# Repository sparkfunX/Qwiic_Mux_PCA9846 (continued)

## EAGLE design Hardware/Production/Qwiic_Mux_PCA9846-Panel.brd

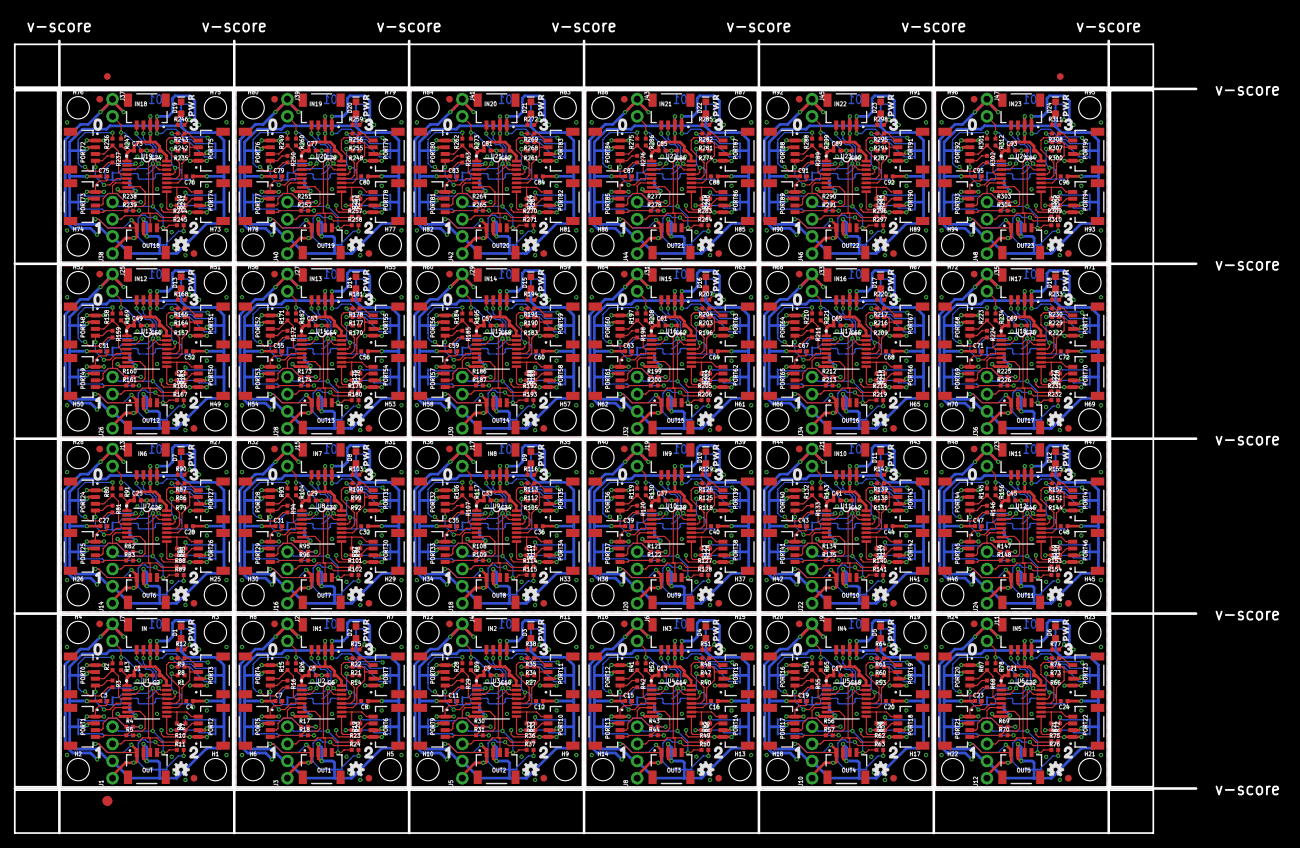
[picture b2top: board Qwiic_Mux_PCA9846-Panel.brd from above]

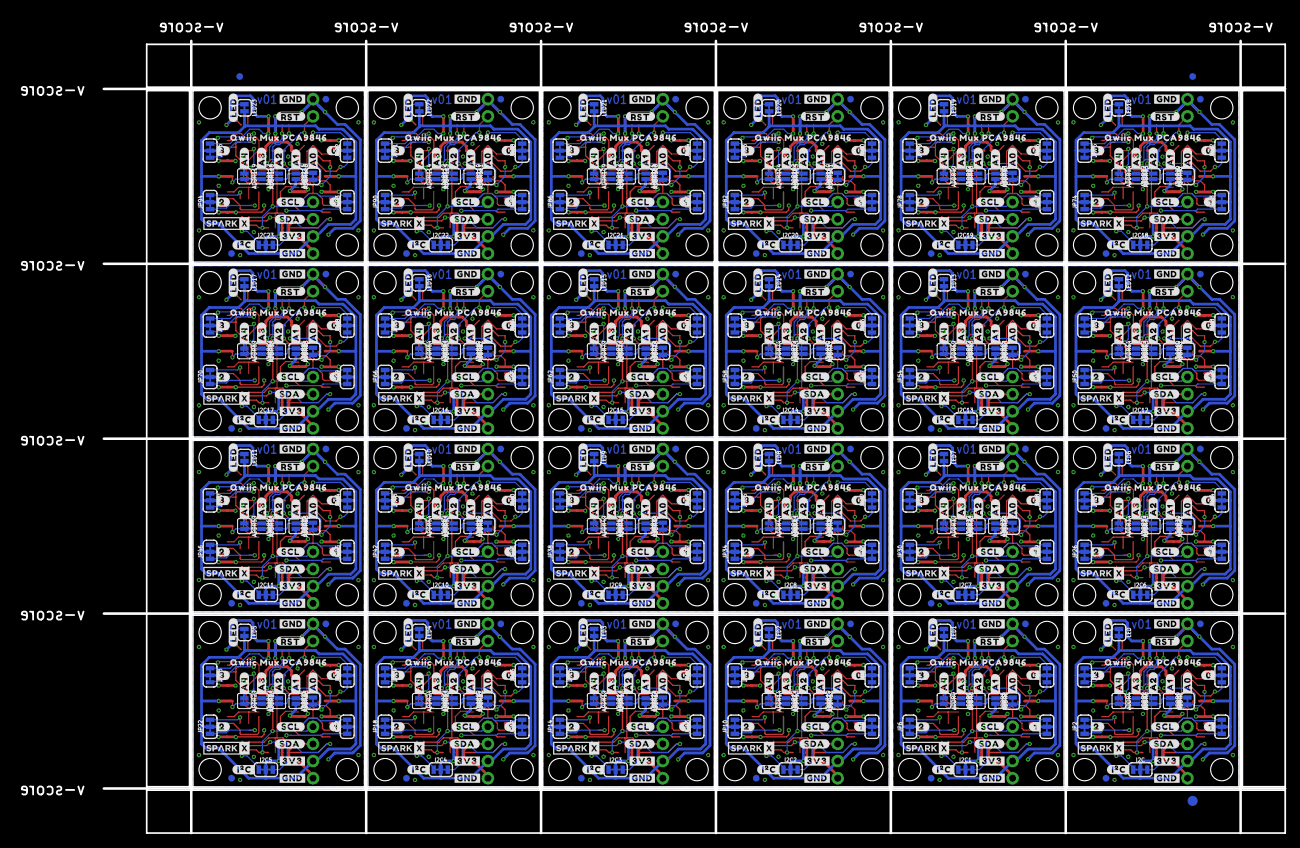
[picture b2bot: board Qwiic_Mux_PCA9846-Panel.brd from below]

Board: 2 copper layers, 175.0 x 117.3 mm, 1710 parts (771 on the bottom side), 648 nets.

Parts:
ADDR0, ADDR5, ADDR10, ADDR15, ADDR20, ADDR25, ADDR30, ADDR35, ADDR40, ADDR45, ADDR50, ADDR55, ADDR60, ADDR65, ADDR70, ADDR75, ADDR80, ADDR85, ADDR90, ADDR95, ADDR100, ADDR105, ADDR110, ADDR115: JUMPER-SMT_2_NC_TRACE_SILK; SMT-JUMPER_2_NC_TRACE_SILK
ADDR1, ADDR2, ADDR3, ADDR4, ADDR6, ADDR7, ADDR8, ADDR9, ADDR11, ADDR12, ADDR13, ADDR14, ADDR16, ADDR17, ADDR18, ADDR19, ADDR21, ADDR22, ADDR23, ADDR24, ADDR26, ADDR27, ADDR28, ADDR29, ADDR31, ADDR32, ADDR33, ADDR34, ADDR36, ADDR37, ADDR38, ADDR39, ADDR41, ADDR42, ADDR43, ADDR44, ADDR46, ADDR47, ADDR48, ADDR49, ADDR51, ADDR52, ADDR53, ADDR54, ADDR56, ADDR57, ADDR58, ADDR59, ADDR61, ADDR62, ADDR63, ADDR64, ADDR66, ADDR67, ADDR68, ADDR69, ADDR71, ADDR72, ADDR73, ADDR74, ADDR76, ADDR77, ADDR78, ADDR79, ADDR81, ADDR82, ADDR83, ADDR84, ADDR86, ADDR87, ADDR88, ADDR89, ADDR91, ADDR92, ADDR93, ADDR94, ADDR96, ADDR97, ADDR98, ADDR99, ADDR101, ADDR102, ADDR103, ADDR104, ADDR106, ADDR107, ADDR108, ADDR109, ADDR111, ADDR112, ADDR113, ADDR114, ADDR116, ADDR117, ADDR118, ADDR119: JUMPER-SMT_2_NO_SILK; SMT-JUMPER_2_NO_SILK
C1, C3, C4, C5, C7, C8, C9, C11, C12, C13, C15, C16, C17, C19, C20, C21, C23, C24, C25, C27, C28, C29, C31, C32, C33, C35, C36, C37, C39, C40, C41, C43, C44, C45, C47, C48, C49, C51, C52, C53, C55, C56, C57, C59, C60, C61, C63, C64, C65, C67, C68, C69, C71, C72, C73, C75, C76, C77, C79, C80, C81, C83, C84, C85, C87, C88, C89, C91, C92, C93, C95, C96: 2.2uF; 0402-TIGHT
C2, C6, C10, C14, C18, C22, C26, C30, C34, C38, C42, C46, C50, C54, C58, C62, C66, C70, C74, C78, C82, C86, C90, C94: 0.1uF; 0402-TIGHT
D1, D2, D3, D4, D5, D6, D7, D8, D9, D10, D11, D12, D13, D14, D15, D16, D17, D18, D19, D20, D21, D22, D23, D24: RED; LED-0603
E$1, E$2, E$3, E$4: FIDUCIAL-1X2
E$5, E$6: FIDUCIAL-1.5X3
FD1, FD2, FD3, FD4, FD5, FD6, FD7, FD8, FD9, FD10, FD11, FD12, FD13, FD14, FD15, FD16, FD17, FD18, FD19, FD20, FD21, FD22, FD23, FD24, FD25, FD26, FD27, FD28, FD29, FD30, FD31, FD32, FD33, FD34, FD35, FD36, FD37, FD38, FD39, FD40, FD41, FD42, FD43, FD44, FD45, FD46, FD47, FD48, FD49, FD50, FD51, FD52, FD53, FD54, FD55, FD56, FD57, FD58, FD59, FD60, FD61, FD62, FD63, FD64, FD65, FD66, FD67, FD68, FD69, FD70, FD71, FD72, FD73, FD74, FD75, FD76, FD77, FD78, FD79, FD80, FD81, FD82, FD83, FD84, FD85, FD86, FD87, FD88, FD89, FD90, FD91, FD92, FD93, FD94, FD95, FD96: FIDUCIAL1X2; FIDUCIAL-1X2
H1, H2, H3, H4, H5, H6, H7, H8, H9, H10, H11, H12, H13, H14, H15, H16, H17, H18, H19, H20, H21, H22, H23, H24, H25, H26, H27, H28, H29, H30, H31, H32, H33, H34, H35, H36, H37, H38, H39, H40, H41, H42, H43, H44, H45, H46, H47, H48, H49, H50, H51, H52, H53, H54, H55, H56, H57, H58, H59, H60, H61, H62, H63, H64, H65, H66, H67, H68, H69, H70, H71, H72, H73, H74, H75, H76, H77, H78, H79, H80, H81, H82, H83, H84, H85, H86, H87, H88, H89, H90, H91, H92, H93, H94, H95, H96: STAND-OFF
I2C, I2C1, I2C2, I2C3, I2C4, I2C5, I2C6, I2C7, I2C8, I2C9, I2C10, I2C11, I2C12, I2C13, I2C14, I2C15, I2C16, I2C17, I2C18, I2C19, I2C20, I2C21, I2C22, I2C23: JUMPER-SMT_3_2-NC_TRACE_SILK; SMT-JUMPER_3_2-NC_TRACE_SILK
IN, IN1, IN2, IN3, IN4, IN5, IN6, IN7, IN8, IN9, IN10, IN11, IN12, IN13, IN14, IN15, IN16, IN17, IN18, IN19, IN20, IN21, IN22, IN23: QWIIC_RIGHT_ANGLE; JST04_1MM_RA
J1, J3, J5, J8, J10, J12, J14, J16, J18, J20, J22, J24, J26, J28, J30, J32, J34, J36, J38, J40, J42, J44, J46, J48: 1X04_NO_SILK
J2, J4, J6, J7, J9, J11, J13, J15, J17, J19, J21, J23, J25, J27, J29, J31, J33, J35, J37, J39, J41, J43, J45, J47: 1X02_NO_SILK
JP0, JP1, JP2, JP3, JP4, JP5, JP6, JP7, JP8, JP9, JP10, JP11, JP12, JP13, JP14, JP15, JP16, JP17, JP18, JP19, JP20, JP21, JP22, JP23, JP24, JP25, JP26, JP27, JP28, JP29, JP30, JP31, JP32, JP33, JP34, JP35, JP36, JP37, JP38, JP39, JP40, JP41, JP42, JP43, JP44, JP45, JP46, JP47, JP48, JP49, JP50, JP51, JP52, JP53, JP54, JP55, JP56, JP57, JP58, JP59, JP60, JP61, JP62, JP63, JP64, JP65, JP66, JP67, JP68, JP69, JP70, JP71, JP72, JP73, JP74, JP75, JP76, JP77, JP78, JP79, JP80, JP81, JP82, JP83, JP84, JP85, JP86, JP87, JP88, JP89, JP90, JP91, JP92, JP93, JP94, JP95: JUMPER-SMT_3_2-NC_TRACE_SILK; SMT-JUMPER_3_2-NC_TRACE_SILK
LED, LED1, LED2, LED3, LED4, LED5, LED6, LED7, LED8, LED9, LED10, LED11, LED12, LED13, LED14, LED15, LED16, LED17, LED18, LED19, LED20, LED21, LED22, LED23: JUMPER-SMT_2_NC_TRACE_SILK; SMT-JUMPER_2_NC_TRACE_SILK
LOGO1, LOGO2, LOGO3, LOGO4, LOGO5, LOGO6, LOGO7, LOGO8, LOGO9, LOGO10, LOGO11, LOGO12, LOGO13, LOGO14, LOGO15, LOGO16, LOGO17, LOGO18, LOGO19, LOGO20, LOGO21, LOGO22, LOGO23, LOGO24: OSHW-LOGOMINI; OSHW-LOGO-MINI
OUT, OUT1, OUT2, OUT3, OUT4, OUT5, OUT6, OUT7, OUT8, OUT9, OUT10, OUT11, OUT12, OUT13, OUT14, OUT15, OUT16, OUT17, OUT18, OUT19, OUT20, OUT21, OUT22, OUT23: QWIIC_RIGHT_ANGLE; JST04_1MM_RA
PORT0, PORT1, PORT2, PORT3, PORT4, PORT5, PORT6, PORT7, PORT8, PORT9, PORT10, PORT11, PORT12, PORT13, PORT14, PORT15, PORT16, PORT17, PORT18, PORT19, PORT20, PORT21, PORT22, PORT23, PORT24, PORT25, PORT26, PORT27, PORT28, PORT29, PORT30, PORT31, PORT32, PORT33, PORT34, PORT35, PORT36, PORT37, PORT38, PORT39, PORT40, PORT41, PORT42, PORT43, PORT44, PORT45, PORT46, PORT47, PORT48, PORT49, PORT50, PORT51, PORT52, PORT53, PORT54, PORT55, PORT56, PORT57, PORT58, PORT59, PORT60, PORT61, PORT62, PORT63, PORT64, PORT65, PORT66, PORT67, PORT68, PORT69, PORT70, PORT71, PORT72, PORT73, PORT74, PORT75, PORT76, PORT77, PORT78, PORT79, PORT80, PORT81, PORT82, PORT83, PORT84, PORT85, PORT86, PORT87, PORT88, PORT89, PORT90, PORT91, PORT92, PORT93, PORT94, PORT95: QWIIC_RIGHT_ANGLE; JST04_1MM_RA
R1, R13, R14, R26, R27, R39, R40, R52, R53, R65, R66, R78, R79, R91, R92, R104, R105, R117, R118, R130, R131, R143, R144, R156, R157, R169, R170, R182, R183, R195, R196, R208, R209, R221, R222, R234, R235, R247, R248, R260, R261, R273, R274, R286, R287, R299, R300, R312: 100k; 0402-TIGHT
R2, R3, R4, R5, R6, R7, R8, R9, R10, R11, R15, R16, R17, R18, R19, R20, R21, R22, R23, R24, R28, R29, R30, R31, R32, R33, R34, R35, R36, R37, R41, R42, R43, R44, R45, R46, R47, R48, R49, R50, R54, R55, R56, R57, R58, R59, R60, R61, R62, R63, R67, R68, R69, R70, R71, R72, R73, R74, R75, R76, R80, R81, R82, R83, R84, R85, R86, R87, R88, R89, R93, R94, R95, R96, R97, R98, R99, R100, R101, R102, R106, R107, R108, R109, R110, R111, R112, R113, R114, R115, R119, R120, R121, R122, R123, R124, R125, R126, R127, R128, R132, R133, R134, R135, R136, R137, R138, R139, R140, R141, R145, R146, R147, R148, R149, R150, R151, R152, R153, R154, R158, R159, R160, R161, R162, R163, R164, R165, R166, R167, R171, R172, R173, R174, R175, R176, R177, R178, R179, R180, R184, R185, R186, R187, R188, R189, R190, R191, R192, R193, R197, R198, R199, R200, R201, R202, R203, R204, R205, R206, R210, R211, R212, R213, R214, R215, R216, R217, R218, R219, R223, R224, R225, R226, R227, R228, R229, R230, R231, R232, R236, R237, R238, R239, R240, R241, R242, R243, R244, R245, R249, R250, R251, R252, R253, R254, R255, R256, R257, R258, R262, R263, R264, R265, R266, R267, R268, R269, R270, R271, R275, R276, R277, R278, R279, R280, R281, R282, R283, R284, R288, R289, R290, R291, R292, R293, R294, R295, R296, R297, R301, R302, R303, R304, R305, R306, R307, R308, R309, R310: 2.2k; 0402-TIGHT
R12, R25, R38, R51, R64, R77, R90, R103, R116, R129, R142, R155, R168, R181, R194, R207, R220, R233, R246, R259, R272, R285, R298, R311: 1k; 0402-TIGHT
U1, U2, U3, U4, U5, U6, U7, U8, U9, U10, U11, U12, U13, U14, U15, U16, U17, U18, U19, U20, U21, U22, U23, U24: PCA9846; SOT403-1
U$1, U$20, U$49, U$73, U$97, U$121, U$145, U$169, U$193, U$217, U$241, U$265, U$289, U$313, U$337, U$361, U$385, U$409, U$433, U$457, U$481, U$505, U$529, U$553: SPARKX-LOGO3; SPARKX-SMALL
U$2, U$26, U$50, U$74, U$98, U$122, U$146, U$170, U$194, U$218, U$242, U$266, U$290, U$314, U$338, U$362, U$386, U$410, U$434, U$458, U$482, U$506, U$530, U$554: PWR43214
U$3, U$27, U$51, U$75, U$99, U$123, U$147, U$171, U$195, U$219, U$243, U$267, U$291, U$315, U$339, U$363, U$387, U$411, U$435, U$459, U$483, U$507, U$531, U$555: 043215
U$4, U$28, U$52, U$76, U$100, U$124, U$148, U$172, U$196, U$220, U$244, U$268, U$292, U$316, U$340, U$364, U$388, U$412, U$436, U$460, U$484, U$508, U$532, U$556: 10
U$5, U$29, U$53, U$77, U$101, U$125, U$149, U$173, U$197, U$221, U$245, U$269, U$293, U$317, U$341, U$365, U$389, U$413, U$437, U$461, U$485, U$509, U$533, U$557: 211
U$6, U$30, U$54, U$78, U$102, U$126, U$150, U$174, U$198, U$222, U$246, U$270, U$294, U$318, U$342, U$366, U$390, U$414, U$438, U$462, U$486, U$510, U$534, U$558: 3212
U$7, U$31, U$55, U$79, U$103, U$127, U$151, U$175, U$199, U$223, U$247, U$271, U$295, U$319, U$343, U$367, U$391, U$415, U$439, U$463, U$487, U$511, U$535, U$559: ##RST##8
U$8, U$32, U$56, U$80, U$104, U$128, U$152, U$176, U$200, U$224, U$248, U$272, U$296, U$320, U$344, U$368, U$392, U$416, U$440, U$464, U$488, U$512, U$536, U$560: #0#9
U$9, U$33, U$57, U$81, U$105, U$129, U$153, U$177, U$201, U$225, U$249, U$273, U$297, U$321, U$345, U$369, U$393, U$417, U$441, U$465, U$489, U$513, U$537, U$561: #1#9
U$10, U$34, U$58, U$82, U$106, U$130, U$154, U$178, U$202, U$226, U$250, U$274, U$298, U$322, U$346, U$370, U$394, U$418, U$442, U$466, U$490, U$514, U$538, U$562: #2#9
U$11, U$35, U$59, U$83, U$107, U$131, U$155, U$179, U$203, U$227, U$251, U$275, U$299, U$323, U$347, U$371, U$395, U$419, U$443, U$467, U$491, U$515, U$539, U$563: #3#9
U$12, U$36, U$60, U$84, U$108, U$132, U$156, U$180, U$204, U$228, U$252, U$276, U$300, U$324, U$348, U$372, U$396, U$420, U$444, U$468, U$492, U$516, U$540, U$564: #3V3#7
U$13, U$37, U$61, U$85, U$109, U$133, U$157, U$181, U$205, U$229, U$253, U$277, U$301, U$325, U$349, U$373, U$397, U$421, U$445, U$469, U$493, U$517, U$541, U$565: #A0#0
U$14, U$38, U$62, U$86, U$110, U$134, U$158, U$182, U$206, U$230, U$254, U$278, U$302, U$326, U$350, U$374, U$398, U$422, U$446, U$470, U$494, U$518, U$542, U$566: #A1#1
U$15, U$39, U$63, U$87, U$111, U$135, U$159, U$183, U$207, U$231, U$255, U$279, U$303, U$327, U$351, U$375, U$399, U$423, U$447, U$471, U$495, U$519, U$543, U$567: #A2#2
U$16, U$40, U$64, U$88, U$112, U$136, U$160, U$184, U$208, U$232, U$256, U$280, U$304, U$328, U$352, U$376, U$400, U$424, U$448, U$472, U$496, U$520, U$544, U$568: #A3#3
U$17, U$41, U$65, U$89, U$113, U$137, U$161, U$185, U$209, U$233, U$257, U$281, U$305, U$329, U$353, U$377, U$401, U$425, U$449, U$473, U$497, U$521, U$545, U$569: #A4#4
U$18, U$19, U$42, U$43, U$66, U$67, U$90, U$91, U$114, U$115, U$138, U$139, U$162, U$163, U$186, U$187, U$210, U$211, U$234, U$235, U$258, U$259, U$282, U$283, U$306, U$307, U$330, U$331, U$354, U$355, U$378, U$379, U$402, U$403, U$426, U$427, U$450, U$451, U$474, U$475, U$498, U$499, U$522, U$523, U$546, U$547, U$570, U$571: #GND#7
U$21, U$44, U$68, U$92, U$116, U$140, U$164, U$188, U$212, U$236, U$260, U$284, U$308, U$332, U$356, U$380, U$404, U$428, U$452, U$476, U$500, U$524, U$548, U$572: #SCL#5
U$22, U$45, U$69, U$93, U$117, U$141, U$165, U$189, U$213, U$237, U$261, U$285, U$309, U$333, U$357, U$381, U$405, U$429, U$453, U$477, U$501, U$525, U$549, U$573: #SDA#6
U$23, U$46, U$70, U$94, U$118, U$142, U$166, U$190, U$214, U$238, U$262, U$286, U$310, U$334, U$358, U$382, U$406, U$430, U$454, U$478, U$502, U$526, U$550, U$574: #LED#0
U$24, U$47, U$71, U$95, U$119, U$143, U$167, U$191, U$215, U$239, U$263, U$287, U$311, U$335, U$359, U$383, U$407, U$431, U$455, U$479, U$503, U$527, U$551, U$575: QWIIC_MUX_PCA98461
U$25, U$48, U$72, U$96, U$120, U$144, U$168, U$192, U$216, U$240, U$264, U$288, U$312, U$336, U$360, U$384, U$408, U$432, U$456, U$480, U$504, U$528, U$552, U$576: #I�C#0

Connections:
3.3V: ADDR3.2, ADDR4.2, C1.1, C2.1, C3.1, C4.1, I2C.2, IN.2, J1.2, JP0.2, JP1.2, JP2.2, JP3.2, LED.2, OUT.2, PORT0.2, PORT1.2, PORT2.2, PORT3.2, R13.2, U1.1, U1.16
3.3V1: ADDR8.2, ADDR9.2, C5.1, C6.1, C7.1, C8.1, I2C1.2, IN1.2, J3.2, JP4.2, JP5.2, JP6.2, JP7.2, LED1.2, OUT1.2, PORT4.2, PORT5.2, PORT6.2, PORT7.2, R26.2, U2.1, U2.16
3.3V2: ADDR13.2, ADDR14.2, C9.1, C10.1, C11.1, C12.1, I2C2.2, IN2.2, J5.2, JP8.2, JP9.2, JP10.2, JP11.2, LED2.2, OUT2.2, PORT8.2, PORT9.2, PORT10.2, PORT11.2, R39.2, U3.1, U3.16
3.3V3: ADDR18.2, ADDR19.2, C13.1, C14.1, C15.1, C16.1, I2C3.2, IN3.2, J8.2, JP12.2, JP13.2, JP14.2, JP15.2, LED3.2, OUT3.2, PORT12.2, PORT13.2, PORT14.2, PORT15.2, R52.2, U4.1, U4.16
3.3V4: ADDR23.2, ADDR24.2, C17.1, C18.1, C19.1, C20.1, I2C4.2, IN4.2, J10.2, JP16.2, JP17.2, JP18.2, JP19.2, LED4.2, OUT4.2, PORT16.2, PORT17.2, PORT18.2, PORT19.2, R65.2, U5.1, U5.16
3.3V5: ADDR28.2, ADDR29.2, C21.1, C22.1, C23.1, C24.1, I2C5.2, IN5.2, J12.2, JP20.2, JP21.2, JP22.2, JP23.2, LED5.2, OUT5.2, PORT20.2, PORT21.2, PORT22.2, PORT23.2, R78.2, U6.1, U6.16
3.3V6: ADDR33.2, ADDR34.2, C25.1, C26.1, C27.1, C28.1, I2C6.2, IN6.2, J14.2, JP24.2, JP25.2, JP26.2, JP27.2, LED6.2, OUT6.2, PORT24.2, PORT25.2, PORT26.2, PORT27.2, R91.2, U7.1, U7.16
3.3V7: ADDR38.2, ADDR39.2, C29.1, C30.1, C31.1, C32.1, I2C7.2, IN7.2, J16.2, JP28.2, JP29.2, JP30.2, JP31.2, LED7.2, OUT7.2, PORT28.2, PORT29.2, PORT30.2, PORT31.2, R104.2, U8.1, U8.16
3.3V8: ADDR43.2, ADDR44.2, C33.1, C34.1, C35.1, C36.1, I2C8.2, IN8.2, J18.2, JP32.2, JP33.2, JP34.2, JP35.2, LED8.2, OUT8.2, PORT32.2, PORT33.2, PORT34.2, PORT35.2, R117.2, U9.1, U9.16
3.3V9: ADDR48.2, ADDR49.2, C37.1, C38.1, C39.1, C40.1, I2C9.2, IN9.2, J20.2, JP36.2, JP37.2, JP38.2, JP39.2, LED9.2, OUT9.2, PORT36.2, PORT37.2, PORT38.2, PORT39.2, R130.2, U10.1, U10.16
3.3V10: ADDR53.2, ADDR54.2, C41.1, C42.1, C43.1, C44.1, I2C10.2, IN10.2, J22.2, JP40.2, JP41.2, JP42.2, JP43.2, LED10.2, OUT10.2, PORT40.2, PORT41.2, PORT42.2, PORT43.2, R143.2, U11.1, U11.16
3.3V11: ADDR58.2, ADDR59.2, C45.1, C46.1, C47.1, C48.1, I2C11.2, IN11.2, J24.2, JP44.2, JP45.2, JP46.2, JP47.2, LED11.2, OUT11.2, PORT44.2, PORT45.2, PORT46.2, PORT47.2, R156.2, U12.1, U12.16
3.3V12: ADDR63.2, ADDR64.2, C49.1, C50.1, C51.1, C52.1, I2C12.2, IN12.2, J26.2, JP48.2, JP49.2, JP50.2, JP51.2, LED12.2, OUT12.2, PORT48.2, PORT49.2, PORT50.2, PORT51.2, R169.2, U13.1, U13.16
3.3V13: ADDR68.2, ADDR69.2, C53.1, C54.1, C55.1, C56.1, I2C13.2, IN13.2, J28.2, JP52.2, JP53.2, JP54.2, JP55.2, LED13.2, OUT13.2, PORT52.2, PORT53.2, PORT54.2, PORT55.2, R182.2, U14.1, U14.16
3.3V14: ADDR73.2, ADDR74.2, C57.1, C58.1, C59.1, C60.1, I2C14.2, IN14.2, J30.2, JP56.2, JP57.2, JP58.2, JP59.2, LED14.2, OUT14.2, PORT56.2, PORT57.2, PORT58.2, PORT59.2, R195.2, U15.1, U15.16
3.3V15: ADDR78.2, ADDR79.2, C61.1, C62.1, C63.1, C64.1, I2C15.2, IN15.2, J32.2, JP60.2, JP61.2, JP62.2, JP63.2, LED15.2, OUT15.2, PORT60.2, PORT61.2, PORT62.2, PORT63.2, R208.2, U16.1, U16.16
3.3V16: ADDR83.2, ADDR84.2, C65.1, C66.1, C67.1, C68.1, I2C16.2, IN16.2, J34.2, JP64.2, JP65.2, JP66.2, JP67.2, LED16.2, OUT16.2, PORT64.2, PORT65.2, PORT66.2, PORT67.2, R221.2, U17.1, U17.16
3.3V17: ADDR88.2, ADDR89.2, C69.1, C70.1, C71.1, C72.1, I2C17.2, IN17.2, J36.2, JP68.2, JP69.2, JP70.2, JP71.2, LED17.2, OUT17.2, PORT68.2, PORT69.2, PORT70.2, PORT71.2, R234.2, U18.1, U18.16
3.3V18: ADDR93.2, ADDR94.2, C73.1, C74.1, C75.1, C76.1, I2C18.2, IN18.2, J38.2, JP72.2, JP73.2, JP74.2, JP75.2, LED18.2, OUT18.2, PORT72.2, PORT73.2, PORT74.2, PORT75.2, R247.2, U19.1, U19.16
3.3V19: ADDR98.2, ADDR99.2, C77.1, C78.1, C79.1, C80.1, I2C19.2, IN19.2, J40.2, JP76.2, JP77.2, JP78.2, JP79.2, LED19.2, OUT19.2, PORT76.2, PORT77.2, PORT78.2, PORT79.2, R260.2, U20.1, U20.16
3.3V20: ADDR103.2, ADDR104.2, C81.1, C82.1, C83.1, C84.1, I2C20.2, IN20.2, J42.2, JP80.2, JP81.2, JP82.2, JP83.2, LED20.2, OUT20.2, PORT80.2, PORT81.2, PORT82.2, PORT83.2, R273.2, U21.1, U21.16
3.3V21: ADDR108.2, ADDR109.2, C85.1, C86.1, C87.1, C88.1, I2C21.2, IN21.2, J44.2, JP84.2, JP85.2, JP86.2, JP87.2, LED21.2, OUT21.2, PORT84.2, PORT85.2, PORT86.2, PORT87.2, R286.2, U22.1, U22.16
3.3V22: ADDR113.2, ADDR114.2, C89.1, C90.1, C91.1, C92.1, I2C22.2, IN22.2, J46.2, JP88.2, JP89.2, JP90.2, JP91.2, LED22.2, OUT22.2, PORT88.2, PORT89.2, PORT90.2, PORT91.2, R299.2, U23.1, U23.16
3.3V23: ADDR118.2, ADDR119.2, C93.1, C94.1, C95.1, C96.1, I2C23.2, IN23.2, J48.2, JP92.2, JP93.2, JP94.2, JP95.2, LED23.2, OUT23.2, PORT92.2, PORT93.2, PORT94.2, PORT95.2, R312.2, U24.1, U24.16
!RESET!: J7.2, R13.1, U1.3
!RESET!1: J2.2, R26.1, U2.3
!RESET!2: J4.2, R39.1, U3.3
!RESET!3: J6.2, R52.1, U4.3
!RESET!4: J9.2, R65.1, U5.3
!RESET!5: J11.2, R78.1, U6.3
!RESET!6: J13.2, R91.1, U7.3
!RESET!7: J15.2, R104.1, U8.3
!RESET!8: J17.2, R117.1, U9.3
!RESET!9: J19.2, R130.1, U10.3
!RESET!10: J21.2, R143.1, U11.3
!RESET!11: J23.2, R156.1, U12.3
!RESET!12: J25.2, R169.1, U13.3
!RESET!13: J27.2, R182.1, U14.3
!RESET!14: J29.2, R195.1, U15.3
!RESET!15: J31.2, R208.1, U16.3
!RESET!16: J33.2, R221.1, U17.3
!RESET!17: J35.2, R234.1, U18.3
!RESET!18: J37.2, R247.1, U19.3
!RESET!19: J39.2, R260.1, U20.3
!RESET!20: J41.2, R273.1, U21.3
!RESET!21: J43.2, R286.1, U22.3
!RESET!22: J45.2, R299.1, U23.3
!RESET!23: J47.2, R312.1, U24.3
A0: ADDR0.1, ADDR1.1, ADDR2.1, ADDR3.1, U1.2
A1: ADDR4.1, R1.2, U1.13
A2: ADDR5.1, ADDR6.1, ADDR7.1, ADDR8.1, U2.2
A3: ADDR9.1, R14.2, U2.13
A4: ADDR10.1, ADDR11.1, ADDR12.1, ADDR13.1, U3.2
A5: ADDR14.1, R27.2, U3.13
A6: ADDR15.1, ADDR16.1, ADDR17.1, ADDR18.1, U4.2
A7: ADDR19.1, R40.2, U4.13
A8: ADDR20.1, ADDR21.1, ADDR22.1, ADDR23.1, U5.2
A9: ADDR24.1, R53.2, U5.13
A10: ADDR25.1, ADDR26.1, ADDR27.1, ADDR28.1, U6.2
A11: ADDR29.1, R66.2, U6.13
A12: ADDR30.1, ADDR31.1, ADDR32.1, ADDR33.1, U7.2
A13: ADDR34.1, R79.2, U7.13
A14: ADDR35.1, ADDR36.1, ADDR37.1, ADDR38.1, U8.2
A15: ADDR39.1, R92.2, U8.13
A16: ADDR40.1, ADDR41.1, ADDR42.1, ADDR43.1, U9.2
A17: ADDR44.1, R105.2, U9.13
A18: ADDR45.1, ADDR46.1, ADDR47.1, ADDR48.1, U10.2
A19: ADDR49.1, R118.2, U10.13
A20: ADDR50.1, ADDR51.1, ADDR52.1, ADDR53.1, U11.2
A21: ADDR54.1, R131.2, U11.13
A22: ADDR55.1, ADDR56.1, ADDR57.1, ADDR58.1, U12.2
A23: ADDR59.1, R144.2, U12.13
A24: ADDR60.1, ADDR61.1, ADDR62.1, ADDR63.1, U13.2
A25: ADDR64.1, R157.2, U13.13
A26: ADDR65.1, ADDR66.1, ADDR67.1, ADDR68.1, U14.2
A27: ADDR69.1, R170.2, U14.13
A28: ADDR70.1, ADDR71.1, ADDR72.1, ADDR73.1, U15.2
A29: ADDR74.1, R183.2, U15.13
A30: ADDR75.1, ADDR76.1, ADDR77.1, ADDR78.1, U16.2
A31: ADDR79.1, R196.2, U16.13
A32: ADDR80.1, ADDR81.1, ADDR82.1, ADDR83.1, U17.2
A33: ADDR84.1, R209.2, U17.13
A34: ADDR85.1, ADDR86.1, ADDR87.1, ADDR88.1, U18.2
A35: ADDR89.1, R222.2, U18.13
A36: ADDR90.1, ADDR91.1, ADDR92.1, ADDR93.1, U19.2
A37: ADDR94.1, R235.2, U19.13
A38: ADDR95.1, ADDR96.1, ADDR97.1, ADDR98.1, U20.2
A39: ADDR99.1, R248.2, U20.13
A40: ADDR100.1, ADDR101.1, ADDR102.1, ADDR103.1, U21.2
A41: ADDR104.1, R261.2, U21.13
A42: ADDR105.1, ADDR106.1, ADDR107.1, ADDR108.1, U22.2
A43: ADDR109.1, R274.2, U22.13
A44: ADDR110.1, ADDR111.1, ADDR112.1, ADDR113.1, U23.2
A45: ADDR114.1, R287.2, U23.13
A46: ADDR115.1, ADDR116.1, ADDR117.1, ADDR118.1, U24.2
A47: ADDR119.1, R300.2, U24.13
GND: ADDR1.2, C1.2, C2.2, C3.2, C4.2, D1.C, IN.1, J1.1, J7.1, OUT.1, PORT0.1, PORT1.1, PORT2.1, PORT3.1, R1.1, U1.8
GND1: ADDR6.2, C5.2, C6.2, C7.2, C8.2, D2.C, IN1.1, J2.1, J3.1, OUT1.1, PORT4.1, PORT5.1, PORT6.1, PORT7.1, R14.1, U2.8
GND2: ADDR11.2, C9.2, C10.2, C11.2, C12.2, D3.C, IN2.1, J4.1, J5.1, OUT2.1, PORT8.1, PORT9.1, PORT10.1, PORT11.1, R27.1, U3.8
GND3: ADDR16.2, C13.2, C14.2, C15.2, C16.2, D4.C, IN3.1, J6.1, J8.1, OUT3.1, PORT12.1, PORT13.1, PORT14.1, PORT15.1, R40.1, U4.8
GND4: ADDR21.2, C17.2, C18.2, C19.2, C20.2, D5.C, IN4.1, J9.1, J10.1, OUT4.1, PORT16.1, PORT17.1, PORT18.1, PORT19.1, R53.1, U5.8
GND5: ADDR26.2, C21.2, C22.2, C23.2, C24.2, D6.C, IN5.1, J11.1, J12.1, OUT5.1, PORT20.1, PORT21.1, PORT22.1, PORT23.1, R66.1, U6.8
GND6: ADDR31.2, C25.2, C26.2, C27.2, C28.2, D7.C, IN6.1, J13.1, J14.1, OUT6.1, PORT24.1, PORT25.1, PORT26.1, PORT27.1, R79.1, U7.8
GND7: ADDR36.2, C29.2, C30.2, C31.2, C32.2, D8.C, IN7.1, J15.1, J16.1, OUT7.1, PORT28.1, PORT29.1, PORT30.1, PORT31.1, R92.1, U8.8
GND8: ADDR41.2, C33.2, C34.2, C35.2, C36.2, D9.C, IN8.1, J17.1, J18.1, OUT8.1, PORT32.1, PORT33.1, PORT34.1, PORT35.1, R105.1, U9.8
GND9: ADDR46.2, C37.2, C38.2, C39.2, C40.2, D10.C, IN9.1, J19.1, J20.1, OUT9.1, PORT36.1, PORT37.1, PORT38.1, PORT39.1, R118.1, U10.8
GND10: ADDR51.2, C41.2, C42.2, C43.2, C44.2, D11.C, IN10.1, J21.1, J22.1, OUT10.1, PORT40.1, PORT41.1, PORT42.1, PORT43.1, R131.1, U11.8
GND11: ADDR56.2, C45.2, C46.2, C47.2, C48.2, D12.C, IN11.1, J23.1, J24.1, OUT11.1, PORT44.1, PORT45.1, PORT46.1, PORT47.1, R144.1, U12.8
GND12: ADDR61.2, C49.2, C50.2, C51.2, C52.2, D13.C, IN12.1, J25.1, J26.1, OUT12.1, PORT48.1, PORT49.1, PORT50.1, PORT51.1, R157.1, U13.8
GND13: ADDR66.2, C53.2, C54.2, C55.2, C56.2, D14.C, IN13.1, J27.1, J28.1, OUT13.1, PORT52.1, PORT53.1, PORT54.1, PORT55.1, R170.1, U14.8
GND14: ADDR71.2, C57.2, C58.2, C59.2, C60.2, D15.C, IN14.1, J29.1, J30.1, OUT14.1, PORT56.1, PORT57.1, PORT58.1, PORT59.1, R183.1, U15.8
GND15: ADDR76.2, C61.2, C62.2, C63.2, C64.2, D16.C, IN15.1, J31.1, J32.1, OUT15.1, PORT60.1, PORT61.1, PORT62.1, PORT63.1, R196.1, U16.8
GND16: ADDR81.2, C65.2, C66.2, C67.2, C68.2, D17.C, IN16.1, J33.1, J34.1, OUT16.1, PORT64.1, PORT65.1, PORT66.1, PORT67.1, R209.1, U17.8
GND17: ADDR86.2, C69.2, C70.2, C71.2, C72.2, D18.C, IN17.1, J35.1, J36.1, OUT17.1, PORT68.1, PORT69.1, PORT70.1, PORT71.1, R222.1, U18.8
GND18: ADDR91.2, C73.2, C74.2, C75.2, C76.2, D19.C, IN18.1, J37.1, J38.1, OUT18.1, PORT72.1, PORT73.1, PORT74.1, PORT75.1, R235.1, U19.8
GND19: ADDR96.2, C77.2, C78.2, C79.2, C80.2, D20.C, IN19.1, J39.1, J40.1, OUT19.1, PORT76.1, PORT77.1, PORT78.1, PORT79.1, R248.1, U20.8
GND20: ADDR101.2, C81.2, C82.2, C83.2, C84.2, D21.C, IN20.1, J41.1, J42.1, OUT20.1, PORT80.1, PORT81.1, PORT82.1, PORT83.1, R261.1, U21.8
GND21: ADDR106.2, C85.2, C86.2, C87.2, C88.2, D22.C, IN21.1, J43.1, J44.1, OUT21.1, PORT84.1, PORT85.1, PORT86.1, PORT87.1, R274.1, U22.8
GND22: ADDR111.2, C89.2, C90.2, C91.2, C92.2, D23.C, IN22.1, J45.1, J46.1, OUT22.1, PORT88.1, PORT89.1, PORT90.1, PORT91.1, R287.1, U23.8
GND23: ADDR116.2, C93.2, C94.2, C95.2, C96.2, D24.C, IN23.1, J47.1, J48.1, OUT23.1, PORT92.1, PORT93.1, PORT94.1, PORT95.1, R300.1, U24.8
unnamed: JP0.3, R2.2
unnamed: JP0.1, R3.2
unnamed: JP1.3, R4.2
unnamed: JP1.1, R5.2
unnamed: JP2.3, R6.2
unnamed: JP2.1, R7.2
unnamed: JP3.3, R8.2
unnamed: JP3.1, R9.2
unnamed: I2C.3, R10.2
unnamed: I2C.1, R11.2
unnamed: LED.1, R12.2
unnamed: D1.A, R12.1
unnamed: JP4.3, R15.2
unnamed: JP4.1, R16.2
unnamed: JP5.3, R17.2
unnamed: JP5.1, R18.2
unnamed: JP6.3, R19.2
unnamed: JP6.1, R20.2
unnamed: JP7.3, R21.2
unnamed: JP7.1, R22.2
unnamed: I2C1.3, R23.2
unnamed: I2C1.1, R24.2
unnamed: LED1.1, R25.2
unnamed: D2.A, R25.1
unnamed: JP8.3, R28.2
unnamed: JP8.1, R29.2
unnamed: JP9.3, R30.2
unnamed: JP9.1, R31.2
unnamed: JP10.3, R32.2
unnamed: JP10.1, R33.2
unnamed: JP11.3, R34.2
unnamed: JP11.1, R35.2
unnamed: I2C2.3, R36.2
unnamed: I2C2.1, R37.2
unnamed: LED2.1, R38.2
unnamed: D3.A, R38.1
unnamed: JP12.3, R41.2
unnamed: JP12.1, R42.2
unnamed: JP13.3, R43.2
unnamed: JP13.1, R44.2
unnamed: JP14.3, R45.2
unnamed: JP14.1, R46.2
unnamed: JP15.3, R47.2
unnamed: JP15.1, R48.2
unnamed: I2C3.3, R49.2
unnamed: I2C3.1, R50.2
unnamed: LED3.1, R51.2
unnamed: D4.A, R51.1
unnamed: JP16.3, R54.2
unnamed: JP16.1, R55.2
unnamed: JP17.3, R56.2
unnamed: JP17.1, R57.2
unnamed: JP18.3, R58.2
unnamed: JP18.1, R59.2
unnamed: JP19.3, R60.2
unnamed: JP19.1, R61.2
unnamed: I2C4.3, R62.2
unnamed: I2C4.1, R63.2
unnamed: LED4.1, R64.2
unnamed: D5.A, R64.1
unnamed: JP20.3, R67.2
unnamed: JP20.1, R68.2
unnamed: JP21.3, R69.2
unnamed: JP21.1, R70.2
unnamed: JP22.3, R71.2
unnamed: JP22.1, R72.2
unnamed: JP23.3, R73.2
unnamed: JP23.1, R74.2
unnamed: I2C5.3, R75.2
unnamed: I2C5.1, R76.2
unnamed: LED5.1, R77.2
unnamed: D6.A, R77.1
unnamed: JP24.3, R80.2
unnamed: JP24.1, R81.2
unnamed: JP25.3, R82.2
unnamed: JP25.1, R83.2
unnamed: JP26.3, R84.2
unnamed: JP26.1, R85.2
unnamed: JP27.3, R86.2
unnamed: JP27.1, R87.2
unnamed: I2C6.3, R88.2
unnamed: I2C6.1, R89.2
unnamed: LED6.1, R90.2
unnamed: D7.A, R90.1
unnamed: JP28.3, R93.2
unnamed: JP28.1, R94.2
unnamed: JP29.3, R95.2
unnamed: JP29.1, R96.2
unnamed: JP30.3, R97.2
unnamed: JP30.1, R98.2
unnamed: JP31.3, R99.2
unnamed: JP31.1, R100.2
unnamed: I2C7.3, R101.2
unnamed: I2C7.1, R102.2
unnamed: LED7.1, R103.2
unnamed: D8.A, R103.1
unnamed: JP32.3, R106.2
unnamed: JP32.1, R107.2
unnamed: JP33.3, R108.2
unnamed: JP33.1, R109.2
unnamed: JP34.3, R110.2
unnamed: JP34.1, R111.2
unnamed: JP35.3, R112.2
unnamed: JP35.1, R113.2
unnamed: I2C8.3, R114.2
unnamed: I2C8.1, R115.2
unnamed: LED8.1, R116.2
unnamed: D9.A, R116.1
unnamed: JP36.3, R119.2
unnamed: JP36.1, R120.2
unnamed: JP37.3, R121.2
unnamed: JP37.1, R122.2
unnamed: JP38.3, R123.2
unnamed: JP38.1, R124.2
unnamed: JP39.3, R125.2
unnamed: JP39.1, R126.2
unnamed: I2C9.3, R127.2
unnamed: I2C9.1, R128.2
unnamed: LED9.1, R129.2
unnamed: D10.A, R129.1
unnamed: JP40.3, R132.2
unnamed: JP40.1, R133.2
unnamed: JP41.3, R134.2
unnamed: JP41.1, R135.2
unnamed: JP42.3, R136.2
unnamed: JP42.1, R137.2
unnamed: JP43.3, R138.2
unnamed: JP43.1, R139.2
unnamed: I2C10.3, R140.2
unnamed: I2C10.1, R141.2
unnamed: LED10.1, R142.2
unnamed: D11.A, R142.1
unnamed: JP44.3, R145.2
unnamed: JP44.1, R146.2
unnamed: JP45.3, R147.2
unnamed: JP45.1, R148.2
unnamed: JP46.3, R149.2
unnamed: JP46.1, R150.2
unnamed: JP47.3, R151.2
unnamed: JP47.1, R152.2
unnamed: I2C11.3, R153.2
unnamed: I2C11.1, R154.2
unnamed: LED11.1, R155.2
unnamed: D12.A, R155.1
unnamed: JP48.3, R158.2
unnamed: JP48.1, R159.2
unnamed: JP49.3, R160.2
unnamed: JP49.1, R161.2
unnamed: JP50.3, R162.2
unnamed: JP50.1, R163.2
unnamed: JP51.3, R164.2
unnamed: JP51.1, R165.2
unnamed: I2C12.3, R166.2
unnamed: I2C12.1, R167.2
unnamed: LED12.1, R168.2
unnamed: D13.A, R168.1
unnamed: JP52.3, R171.2
unnamed: JP52.1, R172.2
unnamed: JP53.3, R173.2
unnamed: JP53.1, R174.2
unnamed: JP54.3, R175.2
unnamed: JP54.1, R176.2
unnamed: JP55.3, R177.2
unnamed: JP55.1, R178.2
unnamed: I2C13.3, R179.2
unnamed: I2C13.1, R180.2
unnamed: LED13.1, R181.2
unnamed: D14.A, R181.1
unnamed: JP56.3, R184.2
unnamed: JP56.1, R185.2
unnamed: JP57.3, R186.2
unnamed: JP57.1, R187.2
unnamed: JP58.3, R188.2
unnamed: JP58.1, R189.2
unnamed: JP59.3, R190.2
unnamed: JP59.1, R191.2
unnamed: I2C14.3, R192.2
unnamed: I2C14.1, R193.2
unnamed: LED14.1, R194.2
unnamed: D15.A, R194.1
unnamed: JP60.3, R197.2
unnamed: JP60.1, R198.2
unnamed: JP61.3, R199.2
unnamed: JP61.1, R200.2
unnamed: JP62.3, R201.2
unnamed: JP62.1, R202.2
unnamed: JP63.3, R203.2
unnamed: JP63.1, R204.2
unnamed: I2C15.3, R205.2
unnamed: I2C15.1, R206.2
unnamed: LED15.1, R207.2
unnamed: D16.A, R207.1
unnamed: JP64.3, R210.2
unnamed: JP64.1, R211.2
unnamed: JP65.3, R212.2
unnamed: JP65.1, R213.2
unnamed: JP66.3, R214.2
unnamed: JP66.1, R215.2
unnamed: JP67.3, R216.2
unnamed: JP67.1, R217.2
unnamed: I2C16.3, R218.2
unnamed: I2C16.1, R219.2
unnamed: LED16.1, R220.2
unnamed: D17.A, R220.1
unnamed: JP68.3, R223.2
unnamed: JP68.1, R224.2
unnamed: JP69.3, R225.2
unnamed: JP69.1, R226.2
unnamed: JP70.3, R227.2
unnamed: JP70.1, R228.2
unnamed: JP71.3, R229.2
unnamed: JP71.1, R230.2
unnamed: I2C17.3, R231.2
unnamed: I2C17.1, R232.2
unnamed: LED17.1, R233.2
unnamed: D18.A, R233.1
unnamed: JP72.3, R236.2
unnamed: JP72.1, R237.2
unnamed: JP73.3, R238.2
unnamed: JP73.1, R239.2
unnamed: JP74.3, R240.2
unnamed: JP74.1, R241.2
unnamed: JP75.3, R242.2
unnamed: JP75.1, R243.2
unnamed: I2C18.3, R244.2
unnamed: I2C18.1, R245.2
unnamed: LED18.1, R246.2
unnamed: D19.A, R246.1
unnamed: JP76.3, R249.2
unnamed: JP76.1, R250.2
unnamed: JP77.3, R251.2
unnamed: JP77.1, R252.2
unnamed: JP78.3, R253.2
unnamed: JP78.1, R254.2
unnamed: JP79.3, R255.2
unnamed: JP79.1, R256.2
unnamed: I2C19.3, R257.2
unnamed: I2C19.1, R258.2
unnamed: LED19.1, R259.2
unnamed: D20.A, R259.1
unnamed: JP80.3, R262.2
unnamed: JP80.1, R263.2
unnamed: JP81.3, R264.2
unnamed: JP81.1, R265.2
unnamed: JP82.3, R266.2
unnamed: JP82.1, R267.2
unnamed: JP83.3, R268.2
unnamed: JP83.1, R269.2
unnamed: I2C20.3, R270.2
unnamed: I2C20.1, R271.2
unnamed: LED20.1, R272.2
unnamed: D21.A, R272.1
unnamed: JP84.3, R275.2
unnamed: JP84.1, R276.2
unnamed: JP85.3, R277.2
unnamed: JP85.1, R278.2
unnamed: JP86.3, R279.2
unnamed: JP86.1, R280.2
unnamed: JP87.3, R281.2
unnamed: JP87.1, R282.2
unnamed: I2C21.3, R283.2
unnamed: I2C21.1, R284.2
unnamed: LED21.1, R285.2
unnamed: D22.A, R285.1
unnamed: JP88.3, R288.2
unnamed: JP88.1, R289.2
unnamed: JP89.3, R290.2
unnamed: JP89.1, R291.2
unnamed: JP90.3, R292.2
unnamed: JP90.1, R293.2
unnamed: JP91.3, R294.2
unnamed: JP91.1, R295.2
unnamed: I2C22.3, R296.2
unnamed: I2C22.1, R297.2
unnamed: LED22.1, R298.2
unnamed: D23.A, R298.1
unnamed: JP92.3, R301.2
unnamed: JP92.1, R302.2
unnamed: JP93.3, R303.2
unnamed: JP93.1, R304.2
unnamed: JP94.3, R305.2
unnamed: JP94.1, R306.2
unnamed: JP95.3, R307.2
unnamed: JP95.1, R308.2
unnamed: I2C23.3, R309.2
unnamed: I2C23.1, R310.2
unnamed: LED23.1, R311.2
unnamed: D24.A, R311.1
SC0: PORT0.4, R3.1, U1.5
SC1: PORT1.4, R5.1, U1.7
SC2: PORT2.4, R7.1, U1.10
SC3: PORT3.4, R9.1, U1.12
SC4: PORT4.4, R16.1, U2.5
SC5: PORT5.4, R18.1, U2.7
SC6: PORT6.4, R20.1, U2.10
SC7: PORT7.4, R22.1, U2.12
SC8: PORT8.4, R29.1, U3.5
SC9: PORT9.4, R31.1, U3.7
SC10: PORT10.4, R33.1, U3.10
SC11: PORT11.4, R35.1, U3.12
SC12: PORT12.4, R42.1, U4.5
SC13: PORT13.4, R44.1, U4.7
SC14: PORT14.4, R46.1, U4.10
SC15: PORT15.4, R48.1, U4.12
SC16: PORT16.4, R55.1, U5.5
SC17: PORT17.4, R57.1, U5.7
SC18: PORT18.4, R59.1, U5.10
SC19: PORT19.4, R61.1, U5.12
SC20: PORT20.4, R68.1, U6.5
SC21: PORT21.4, R70.1, U6.7
SC22: PORT22.4, R72.1, U6.10
SC23: PORT23.4, R74.1, U6.12
SC24: PORT24.4, R81.1, U7.5
SC25: PORT25.4, R83.1, U7.7
SC26: PORT26.4, R85.1, U7.10
SC27: PORT27.4, R87.1, U7.12
SC28: PORT28.4, R94.1, U8.5
SC29: PORT29.4, R96.1, U8.7
SC30: PORT30.4, R98.1, U8.10
SC31: PORT31.4, R100.1, U8.12
SC32: PORT32.4, R107.1, U9.5
SC33: PORT33.4, R109.1, U9.7
SC34: PORT34.4, R111.1, U9.10
SC35: PORT35.4, R113.1, U9.12
SC36: PORT36.4, R120.1, U10.5
SC37: PORT37.4, R122.1, U10.7
SC38: PORT38.4, R124.1, U10.10
SC39: PORT39.4, R126.1, U10.12
SC40: PORT40.4, R133.1, U11.5
SC41: PORT41.4, R135.1, U11.7
SC42: PORT42.4, R137.1, U11.10
SC43: PORT43.4, R139.1, U11.12
SC44: PORT44.4, R146.1, U12.5
SC45: PORT45.4, R148.1, U12.7
SC46: PORT46.4, R150.1, U12.10
SC47: PORT47.4, R152.1, U12.12
SC48: PORT48.4, R159.1, U13.5
SC49: PORT49.4, R161.1, U13.7
SC50: PORT50.4, R163.1, U13.10
SC51: PORT51.4, R165.1, U13.12
SC52: PORT52.4, R172.1, U14.5
SC53: PORT53.4, R174.1, U14.7
SC54: PORT54.4, R176.1, U14.10
SC55: PORT55.4, R178.1, U14.12
SC56: PORT56.4, R185.1, U15.5
SC57: PORT57.4, R187.1, U15.7
SC58: PORT58.4, R189.1, U15.10
SC59: PORT59.4, R191.1, U15.12
SC60: PORT60.4, R198.1, U16.5
SC61: PORT61.4, R200.1, U16.7
SC62: PORT62.4, R202.1, U16.10
SC63: PORT63.4, R204.1, U16.12
SC64: PORT64.4, R211.1, U17.5
SC65: PORT65.4, R213.1, U17.7
SC66: PORT66.4, R215.1, U17.10
SC67: PORT67.4, R217.1, U17.12
SC68: PORT68.4, R224.1, U18.5
SC69: PORT69.4, R226.1, U18.7
SC70: PORT70.4, R228.1, U18.10
SC71: PORT71.4, R230.1, U18.12
SC72: PORT72.4, R237.1, U19.5
SC73: PORT73.4, R239.1, U19.7
SC74: PORT74.4, R241.1, U19.10
SC75: PORT75.4, R243.1, U19.12
SC76: PORT76.4, R250.1, U20.5
SC77: PORT77.4, R252.1, U20.7
SC78: PORT78.4, R254.1, U20.10
SC79: PORT79.4, R256.1, U20.12
SC80: PORT80.4, R263.1, U21.5
SC81: PORT81.4, R265.1, U21.7
SC82: PORT82.4, R267.1, U21.10
SC83: PORT83.4, R269.1, U21.12
SC84: PORT84.4, R276.1, U22.5
SC85: PORT85.4, R278.1, U22.7
SC86: PORT86.4, R280.1, U22.10
SC87: PORT87.4, R282.1, U22.12
SC88: PORT88.4, R289.1, U23.5
SC89: PORT89.4, R291.1, U23.7
SC90: PORT90.4, R293.1, U23.10
SC91: PORT91.4, R295.1, U23.12
SC92: PORT92.4, R302.1, U24.5
SC93: PORT93.4, R304.1, U24.7
SC94: PORT94.4, R306.1, U24.10
SC95: PORT95.4, R308.1, U24.12
SCL: ADDR0.2, IN.4, J1.4, OUT.4, R11.1, U1.14
SCL1: ADDR5.2, IN1.4, J3.4, OUT1.4, R24.1, U2.14
SCL2: ADDR10.2, IN2.4, J5.4, OUT2.4, R37.1, U3.14
SCL3: ADDR15.2, IN3.4, J8.4, OUT3.4, R50.1, U4.14
SCL4: ADDR20.2, IN4.4, J10.4, OUT4.4, R63.1, U5.14
SCL5: ADDR25.2, IN5.4, J12.4, OUT5.4, R76.1, U6.14
SCL6: ADDR30.2, IN6.4, J14.4, OUT6.4, R89.1, U7.14
SCL7: ADDR35.2, IN7.4, J16.4, OUT7.4, R102.1, U8.14
SCL8: ADDR40.2, IN8.4, J18.4, OUT8.4, R115.1, U9.14
SCL9: ADDR45.2, IN9.4, J20.4, OUT9.4, R128.1, U10.14
SCL10: ADDR50.2, IN10.4, J22.4, OUT10.4, R141.1, U11.14
SCL11: ADDR55.2, IN11.4, J24.4, OUT11.4, R154.1, U12.14
SCL12: ADDR60.2, IN12.4, J26.4, OUT12.4, R167.1, U13.14
SCL13: ADDR65.2, IN13.4, J28.4, OUT13.4, R180.1, U14.14
SCL14: ADDR70.2, IN14.4, J30.4, OUT14.4, R193.1, U15.14
SCL15: ADDR75.2, IN15.4, J32.4, OUT15.4, R206.1, U16.14
SCL16: ADDR80.2, IN16.4, J34.4, OUT16.4, R219.1, U17.14
SCL17: ADDR85.2, IN17.4, J36.4, OUT17.4, R232.1, U18.14
SCL18: ADDR90.2, IN18.4, J38.4, OUT18.4, R245.1, U19.14
SCL19: ADDR95.2, IN19.4, J40.4, OUT19.4, R258.1, U20.14
SCL20: ADDR100.2, IN20.4, J42.4, OUT20.4, R271.1, U21.14
SCL21: ADDR105.2, IN21.4, J44.4, OUT21.4, R284.1, U22.14
SCL22: ADDR110.2, IN22.4, J46.4, OUT22.4, R297.1, U23.14
SCL23: ADDR115.2, IN23.4, J48.4, OUT23.4, R310.1, U24.14
SD0: PORT0.3, R2.1, U1.4
SD1: PORT1.3, R4.1, U1.6
SD2: PORT2.3, R6.1, U1.9
SD3: PORT3.3, R8.1, U1.11
SD4: PORT4.3, R15.1, U2.4
SD5: PORT5.3, R17.1, U2.6
SD6: PORT6.3, R19.1, U2.9
SD7: PORT7.3, R21.1, U2.11
SD8: PORT8.3, R28.1, U3.4
SD9: PORT9.3, R30.1, U3.6
SD10: PORT10.3, R32.1, U3.9
SD11: PORT11.3, R34.1, U3.11
SD12: PORT12.3, R41.1, U4.4
SD13: PORT13.3, R43.1, U4.6
SD14: PORT14.3, R45.1, U4.9
SD15: PORT15.3, R47.1, U4.11
SD16: PORT16.3, R54.1, U5.4
SD17: PORT17.3, R56.1, U5.6
SD18: PORT18.3, R58.1, U5.9
SD19: PORT19.3, R60.1, U5.11
SD20: PORT20.3, R67.1, U6.4
SD21: PORT21.3, R69.1, U6.6
SD22: PORT22.3, R71.1, U6.9
SD23: PORT23.3, R73.1, U6.11
SD24: PORT24.3, R80.1, U7.4
SD25: PORT25.3, R82.1, U7.6
SD26: PORT26.3, R84.1, U7.9
SD27: PORT27.3, R86.1, U7.11
SD28: PORT28.3, R93.1, U8.4
SD29: PORT29.3, R95.1, U8.6
SD30: PORT30.3, R97.1, U8.9
SD31: PORT31.3, R99.1, U8.11
SD32: PORT32.3, R106.1, U9.4
SD33: PORT33.3, R108.1, U9.6
SD34: PORT34.3, R110.1, U9.9
SD35: PORT35.3, R112.1, U9.11
SD36: PORT36.3, R119.1, U10.4
SD37: PORT37.3, R121.1, U10.6
SD38: PORT38.3, R123.1, U10.9
SD39: PORT39.3, R125.1, U10.11
SD40: PORT40.3, R132.1, U11.4
SD41: PORT41.3, R134.1, U11.6
SD42: PORT42.3, R136.1, U11.9
SD43: PORT43.3, R138.1, U11.11
SD44: PORT44.3, R145.1, U12.4
SD45: PORT45.3, R147.1, U12.6
SD46: PORT46.3, R149.1, U12.9
SD47: PORT47.3, R151.1, U12.11
SD48: PORT48.3, R158.1, U13.4
SD49: PORT49.3, R160.1, U13.6
SD50: PORT50.3, R162.1, U13.9
SD51: PORT51.3, R164.1, U13.11
SD52: PORT52.3, R171.1, U14.4
SD53: PORT53.3, R173.1, U14.6
SD54: PORT54.3, R175.1, U14.9
SD55: PORT55.3, R177.1, U14.11
SD56: PORT56.3, R184.1, U15.4
SD57: PORT57.3, R186.1, U15.6
SD58: PORT58.3, R188.1, U15.9
SD59: PORT59.3, R190.1, U15.11
SD60: PORT60.3, R197.1, U16.4
SD61: PORT61.3, R199.1, U16.6
SD62: PORT62.3, R201.1, U16.9
SD63: PORT63.3, R203.1, U16.11
SD64: PORT64.3, R210.1, U17.4
SD65: PORT65.3, R212.1, U17.6
SD66: PORT66.3, R214.1, U17.9
SD67: PORT67.3, R216.1, U17.11
SD68: PORT68.3, R223.1, U18.4
SD69: PORT69.3, R225.1, U18.6
SD70: PORT70.3, R227.1, U18.9
SD71: PORT71.3, R229.1, U18.11
SD72: PORT72.3, R236.1, U19.4
SD73: PORT73.3, R238.1, U19.6
SD74: PORT74.3, R240.1, U19.9
SD75: PORT75.3, R242.1, U19.11
SD76: PORT76.3, R249.1, U20.4
SD77: PORT77.3, R251.1, U20.6
SD78: PORT78.3, R253.1, U20.9
SD79: PORT79.3, R255.1, U20.11
SD80: PORT80.3, R262.1, U21.4
SD81: PORT81.3, R264.1, U21.6
SD82: PORT82.3, R266.1, U21.9
SD83: PORT83.3, R268.1, U21.11
SD84: PORT84.3, R275.1, U22.4
SD85: PORT85.3, R277.1, U22.6
SD86: PORT86.3, R279.1, U22.9
SD87: PORT87.3, R281.1, U22.11
SD88: PORT88.3, R288.1, U23.4
SD89: PORT89.3, R290.1, U23.6
SD90: PORT90.3, R292.1, U23.9
SD91: PORT91.3, R294.1, U23.11
SD92: PORT92.3, R301.1, U24.4
SD93: PORT93.3, R303.1, U24.6
SD94: PORT94.3, R305.1, U24.9
SD95: PORT95.3, R307.1, U24.11
SDA: ADDR2.2, IN.3, J1.3, OUT.3, R10.1, U1.15
SDA1: ADDR7.2, IN1.3, J3.3, OUT1.3, R23.1, U2.15
SDA2: ADDR12.2, IN2.3, J5.3, OUT2.3, R36.1, U3.15
SDA3: ADDR17.2, IN3.3, J8.3, OUT3.3, R49.1, U4.15
SDA4: ADDR22.2, IN4.3, J10.3, OUT4.3, R62.1, U5.15
SDA5: ADDR27.2, IN5.3, J12.3, OUT5.3, R75.1, U6.15
SDA6: ADDR32.2, IN6.3, J14.3, OUT6.3, R88.1, U7.15
SDA7: ADDR37.2, IN7.3, J16.3, OUT7.3, R101.1, U8.15
SDA8: ADDR42.2, IN8.3, J18.3, OUT8.3, R114.1, U9.15
SDA9: ADDR47.2, IN9.3, J20.3, OUT9.3, R127.1, U10.15
SDA10: ADDR52.2, IN10.3, J22.3, OUT10.3, R140.1, U11.15
SDA11: ADDR57.2, IN11.3, J24.3, OUT11.3, R153.1, U12.15
SDA12: ADDR62.2, IN12.3, J26.3, OUT12.3, R166.1, U13.15
SDA13: ADDR67.2, IN13.3, J28.3, OUT13.3, R179.1, U14.15
SDA14: ADDR72.2, IN14.3, J30.3, OUT14.3, R192.1, U15.15
SDA15: ADDR77.2, IN15.3, J32.3, OUT15.3, R205.1, U16.15
SDA16: ADDR82.2, IN16.3, J34.3, OUT16.3, R218.1, U17.15
SDA17: ADDR87.2, IN17.3, J36.3, OUT17.3, R231.1, U18.15
SDA18: ADDR92.2, IN18.3, J38.3, OUT18.3, R244.1, U19.15
SDA19: ADDR97.2, IN19.3, J40.3, OUT19.3, R257.1, U20.15
SDA20: ADDR102.2, IN20.3, J42.3, OUT20.3, R270.1, U21.15
SDA21: ADDR107.2, IN21.3, J44.3, OUT21.3, R283.1, U22.15
SDA22: ADDR112.2, IN22.3, J46.3, OUT22.3, R296.1, U23.15
SDA23: ADDR117.2, IN23.3, J48.3, OUT23.3, R309.1, U24.15

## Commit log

2023-04-23 Routed
2023-04-24 Ready for review
2023-04-24 Add PROD_ID
2023-06-28 Add README
